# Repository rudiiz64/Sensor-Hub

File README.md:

# Sensor-Hub

__Purpose:__ The purpose of this design is to start with an idea and see it to completion. Realistically, this sensor hub serves no real purpose, as it is mainly a way for me to begin initial schematic design and layout. This design tackles a multitude of areas that needed to be practiced, such as component selection, power distribution, and further acquiring data from datasheets.

This system utilizes an STM32L100 chip with an active reset and boot mode toggle, USB-B receptacle, onboard sensors, which include light intensity, humiditiy, and ambient temperature, an SD card, SWD breakout pins, a +5V to +3.3V linear voltage regulator, a screw terminal to fit a +5V battery with a protective eFuse, and a battery recharge circuit.

__Lessons learned:__ One of the most valuable lessons learned while progressing through this project is to fully understand what the system needs and whether or not those needs can be met. This means providing proper current, minimizing voltage drop due to trace length/width, and also understanding return current. Another notable lesson is that sometimes designs can be a little weird due to component placement. From my experience, the initial component placement will not result in the greatest system, as my original design had a voltage drop of 0.4V in the 3.3V line due to excessive trace lengths. Lastly, I learned that more time needs to be spent on designing the power side in terms of component selection AND feasibility. For instance, the design was originally only USB powered, which made no real sense as these kinds of sensors need to be flexible in terms of placement. Because of this reasoning, a battery was implemented with a battery recharge and a protective eFuse.

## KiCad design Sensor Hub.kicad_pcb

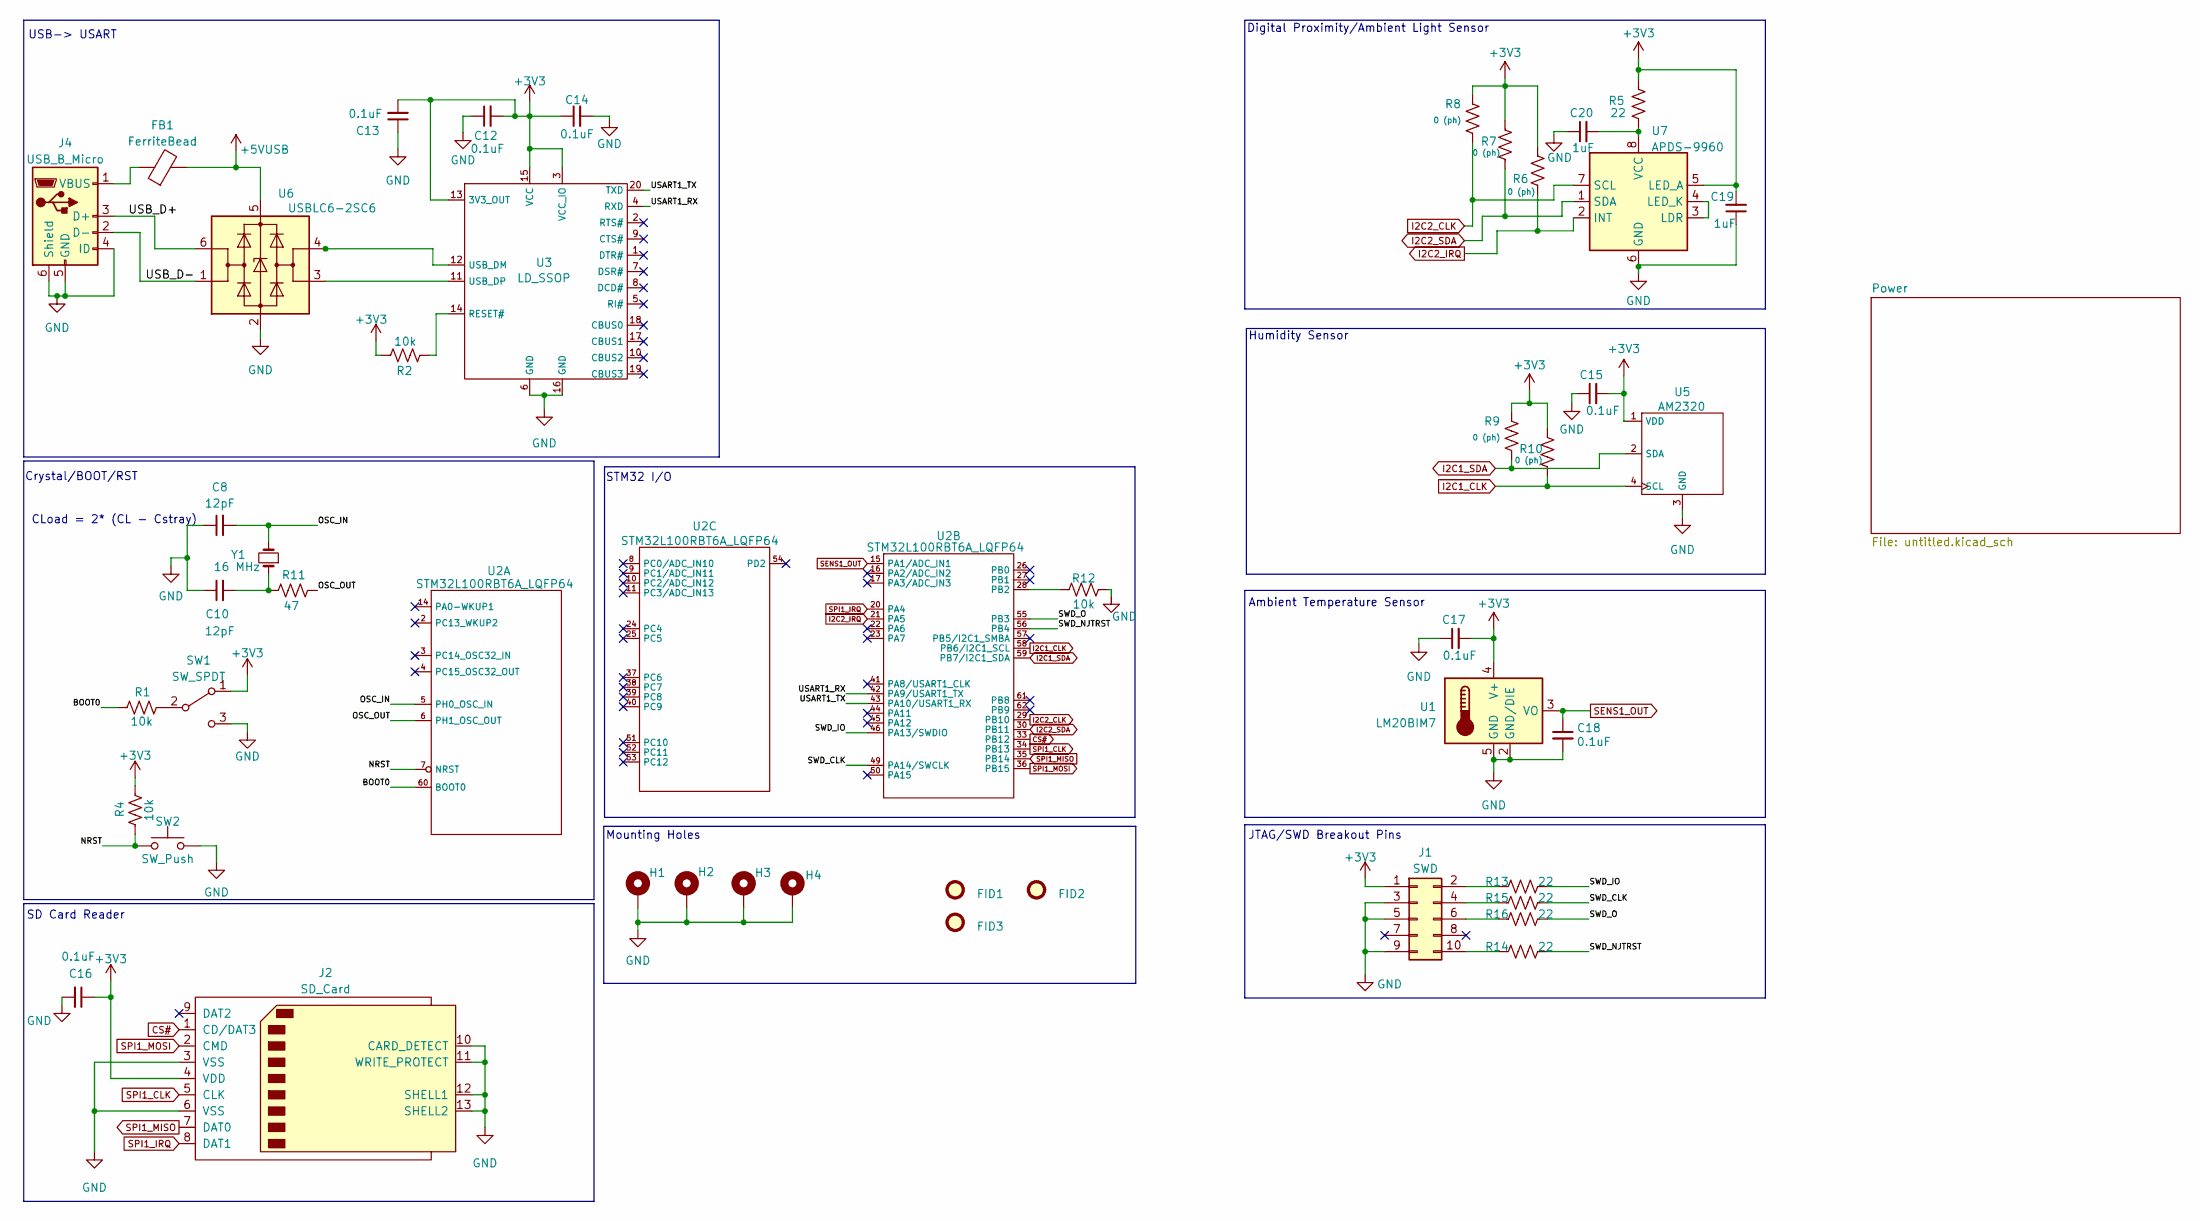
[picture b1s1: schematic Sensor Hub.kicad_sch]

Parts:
C8, C10: 12pF; C_0402_1005Metric
C12, C13, C14, C15, C16, C17, C18: 0.1uF; C_0603_1608Metric
C19, C20: 1uF; C_0603_1608Metric
FB1: FerriteBead; LairdTech_28C0236-0JW-10
FID1, FID2, FID3: Fiducial; Fiducial_1mm_Mask2mm
H1, H2, H3, H4: MountingHole_Pad; MountingHole_2.2mm_M2_Pad_Via
J1: SWD; PinHeader_2x05_P2.00mm_Vertical
J2: SD_Card; SD_Hirose_DM1AA_SF_PEJ82
J4: USB_B_Micro; USB_Micro-B_Amphenol_10118194_Horizontal
R1, R2, R4, R12: 10k; R_0402_1005Metric
R5, R13, R14, R15, R16: 22; R_0402_1005Metric
R6, R7, R8, R9, R10: 0 (ph); R_0402_1005Metric
R11: 47; R_0402_1005Metric
SW1: SW_SPDT; SW_E-Switch_EG1271_SPDT
SW2: SW_Push; SW_PUSH_6mm
U1: LM20BIM7; SOT-353_SC-70-5
U2: STM32L100RBT6A_LQFP64
U3: LD_SSOP; FT231_20_LD_SSOP
U5: AM2320; PinSocket_1x04_P2.00mm_Vertical
U6: USBLC6-2SC6; SOT-23-6
U7: APDS-9960; Avago_APDS-9960
Y1: 16 MHz; Crystal_SMD_0603-2Pin_6.0x3.5mm

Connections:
+3V3: C12.2, C13.2, C14.1, C15.2, C16.1, C17.2, C19.2, J1.1, J2.4 (VDD), R2.1, R4.1, R5.2, R6.2, R7.2, R8.2, R9.2, R10.2, SW1.1 (A), U1.4 (V+), U3.3 (VCC_IO), U3.13 (3V3_OUT), U3.15 (VCC), U5.1 (VDD), U7.5 (LED_A); also elsewhere on the board
+5V: FB1.2, U6.5 (VBUS); also elsewhere on the board
/BOOT0: R1.2, U2.60 (BOOT0)
/NRST: R4.2, SW2.1, U2.7 (NRST)
/OSC_IN: C8.2, U2.5 (PH0_OSC_IN), Y1.2
/OSC_OUT: R11.1, U2.6 (PH1_OSC_OUT)
/SWD_CLK: R15.2, U2.49 (PA14/SWCLK)
/SWD_IO: R13.1, U2.46 (PA13/SWDIO)
/SWD_NJTRST: R14.2, U2.56 (PB4)
/SWD_O: R16.2, U2.55 (PB3)
/USART1_RX: U2.42 (PA9/USART1_TX), U3.4 (RXD)
/USART1_TX: U2.43 (PA10/USART1_RX), U3.20 (TXD)
/USB_D+: J4.3 (D+), U6.6 (I/O1)
/USB_D-: J4.2 (D-), U6.1 (I/O1)
CS#: J2.1 (CD/DAT3), U2.33 (PB12)
GND: C8.1, C10.1, C12.1, C13.1, C14.2, C15.1, C16.2, C17.1, C18.2, C19.1, C20.1, H1.1, H2.1, H3.1, H4.1, J1.3, J1.5, J1.9, J2.3 (VSS), J2.6 (VSS), J2.10 (CARD_DETECT), J2.11 (WRITE_PROTECT), J2.12 (SHELL1), J2.13 (SHELL2), J2.CP, J2.SH, J2.SW, J2.WP, J4.4 (ID), J4.5 (GND), J4.6 (Shield), R12.2, SW1.3 (C), SW2.2, U1.2 (GND/DIE), U1.5 (GND), U3.6 (GND), U3.16 (GND), U5.3 (GND), U6.2 (GND), U7.6 (GND); also elsewhere on the board
I2C1_CLK: R10.1, U2.58 (PB6/I2C1_SCL), U5.4 (SCL)
I2C1_SDA: R9.1, U2.59 (PB7/I2C1_SDA), U5.2 (SDA)
I2C2_CLK: R8.1, U2.29 (PB10), U7.7 (SCL)
I2C2_IRQ: R6.1, U2.21 (PA5), U7.2 (INT)
I2C2_SDA: R7.1, U2.30 (PB11), U7.1 (SDA)
unnamed: C10.2, R11.2, Y1.1
unnamed: J1.2, R13.2
unnamed: J1.4, R15.1
unnamed: J1.6, R16.1
unnamed: J1.10, R14.1
unnamed: FB1.1, J4.1 (VBUS)
unnamed: R1.1, SW1.2 (B)
unnamed: R12.1, U2.28 (PB2)
unnamed: R2.2, U3.14 (RESET#)
unnamed: U3.12 (USB_DM), U6.4 (I/O2)
unnamed: U3.11 (USB_DP), U6.3 (I/O2)
unnamed: U7.3 (LDR), U7.4 (LED_K)
unnamed: C20.2, R5.1, U7.8 (VCC)
SENS1_OUT: C18.1, U1.3 (VO), U2.15 (PA1/ADC_IN1)
SPI1_CLK: J2.5 (CLK), U2.34 (PB13)
SPI1_IRQ: J2.8 (DAT1), U2.20 (PA4)
SPI1_MISO: J2.7 (DAT0), U2.35 (PB14)
SPI1_MOSI: J2.2 (CMD), U2.36 (PB15)

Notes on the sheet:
STM32 I/O
Crystal/BOOT/RST
CLoad = 2* (CL - Cstray)
Mounting Holes
Ambient Temperature Sensor
Digital Proximity/Ambient Light Sensor
JTAG/SWD Breakout Pins
SD Card Reader
Humidity Sensor
USB-> USART

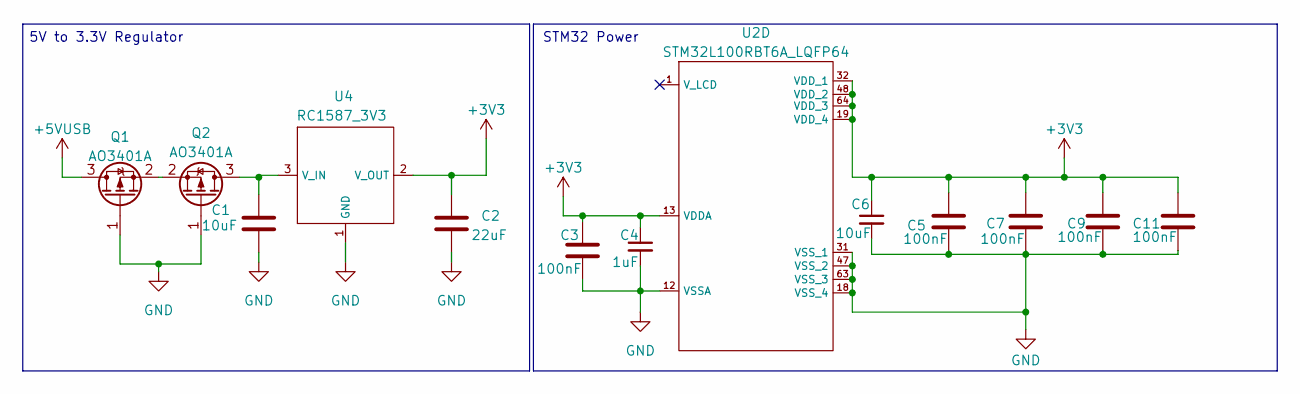
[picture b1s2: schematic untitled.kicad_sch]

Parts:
C1, C6: 10uF; C_0603_1608Metric
C2: 22uF; C_0603_1608Metric
C3, C5, C7, C9, C11: 100nF; C_0402_1005Metric
C4: 1uF; C_0603_1608Metric
Q1, Q2: AO3401A; SOT-23
U2: STM32L100RBT6A_LQFP64
U4: RC1587_3V3; RC1587M3V3T

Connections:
+3V3: C2.1, C3.1, C4.1, C5.1, C6.1, C7.1, C9.1, C11.1, U2.13 (VDDA), U2.19 (VDD_4), U2.32 (VDD_1), U2.48 (VDD_2), U2.64 (VDD_3), U4.2 (V_OUT); also elsewhere on the board
+5V: Q1.3 (D); also elsewhere on the board
GND: C1.2, C2.2, C3.2, C4.2, C5.2, C6.2, C7.2, C9.2, C11.2, Q1.1 (G), Q2.1 (G), U2.12 (VSSA), U2.18 (VSS_4), U2.31 (VSS_1), U2.47 (VSS_2), U2.63 (VSS_3), U4.1 (GND); also elsewhere on the board
unnamed: Q1.2 (S), Q2.2 (S)
unnamed: C1.1, Q2.3 (D), U4.3 (V_IN)

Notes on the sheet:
STM32 Power
5V to 3.3V Regulator

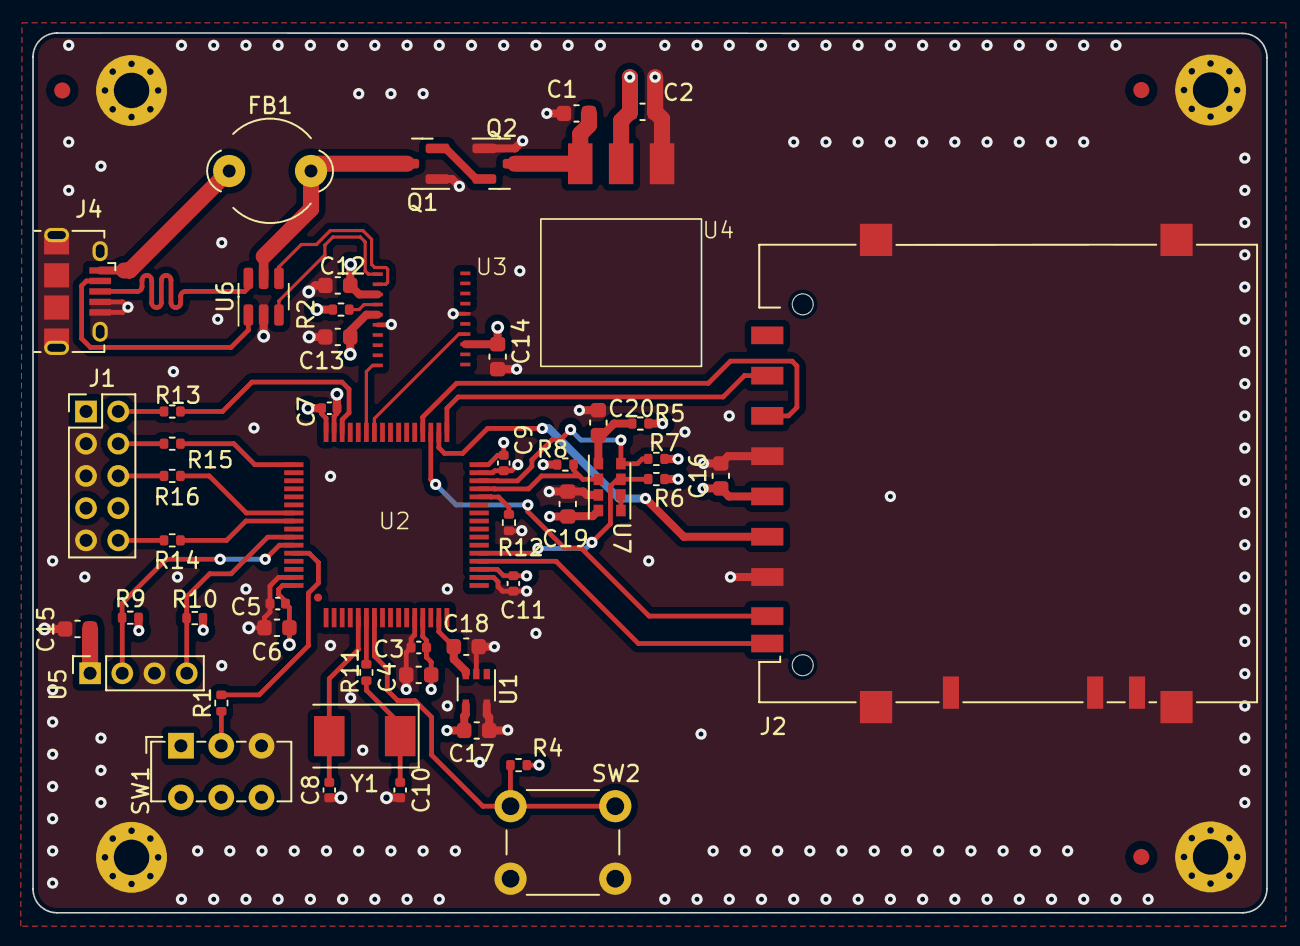
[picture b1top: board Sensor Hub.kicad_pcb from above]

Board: 4 copper layers, 76.6 x 54.6 mm, 58 parts (0 on the bottom side), 41 nets.

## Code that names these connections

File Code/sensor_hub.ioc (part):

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Mcu.Name=STM32H745ZITx
Mcu.Package=LQFP144
Mcu.UserName=STM32H745ZITx
PA1.GPIOParameters=PinAttribute
PA1.Mode=RMII
PA1.PinAttribute=CortexM7
PA1.Signal=ETH_REF_CLK
PA11.GPIOParameters=PinAttribute
PA11.Mode=Device_Only
PA11.PinAttribute=CortexM7
PA11.Signal=USB_OTG_FS_DM
PA12.GPIOParameters=PinAttribute
PA12.Mode=Device_Only
PA12.PinAttribute=CortexM7
PA12.Signal=USB_OTG_FS_DP
PA2.GPIOParameters=PinAttribute
PA2.Mode=RMII
PA2.PinAttribute=CortexM7
PA2.Signal=ETH_MDIO
PA7.GPIOParameters=PinAttribute
PA7.Mode=RMII
PA7.PinAttribute=CortexM7
PA7.Signal=ETH_CRS_DV
PA8.GPIOParameters=PinAttribute
PA8.Mode=Activate_SOF_FS
PA8.PinAttribute=CortexM7
PA8.Signal=USB_OTG_FS_SOF
PA9.GPIOParameters=PinAttribute
PA9.Mode=Activate_VBUS
PA9.PinAttribute=CortexM7
PA9.Signal=USB_OTG_FS_VBUS
PB0.ContextOwner=CortexM7
PB0.GPIOParameters=GPIO_Speed,GPIO_Label,PinAttribute
PB0.GPIO_Label=LD1 [Green Led]
PB0.GPIO_Speed=GPIO_SPEED_FREQ_VERY_HIGH
PB0.PinAttribute=CortexM7
PB0.Signal=GPIO_Output
PB13.GPIOParameters=PinAttribute
PB13.Mode=RMII
PB13.PinAttribute=CortexM7
PB13.Signal=ETH_TXD1
PB14.ContextOwner=CortexM7
PB14.GPIOParameters=GPIO_Speed,GPIO_Label,PinAttribute
PB14.GPIO_Label=LD3 [Red Led]
PB14.GPIO_Speed=GPIO_SPEED_FREQ_VERY_HIGH
PB14.PinAttribute=CortexM7
PB14.Signal=GPIO_Output
PB6.GPIOParameters=PinAttribute
PB6.Mode=I2C
PB6.PinAttribute=CortexM7
PB6.Signal=I2C1_SCL
PB7.GPIOParameters=PinAttribute
PB7.Mode=I2C
PB7.PinAttribute=CortexM7
PB7.Signal=I2C1_SDA
PC1.GPIOParameters=PinAttribute
PC1.Mode=RMII
PC1.PinAttribute=CortexM7
PC1.Signal=ETH_MDC
PC13.GPIOParameters=GPIO_Label,PinAttribute
PC13.GPIO_Label=B1 [Blue PushButton]
PC13.PinAttribute=Free
PC13.Signal=GPIO_Input
PC14-OSC32_IN\ (OSC32_IN).GPIOParameters=PinAttribute
PC14-OSC32_IN\ (OSC32_IN).Mode=LSE-External-Oscillator
PC14-OSC32_IN\ (OSC32_IN).PinAttribute=CortexM7
PC14-OSC32_IN\ (OSC32_IN).Signal=RCC_OSC32_IN
PC15-OSC32_OUT\ (OSC32_OUT).GPIOParameters=PinAttribute
PC15-OSC32_OUT\ (OSC32_OUT).Mode=LSE-External-Oscillator
PC15-OSC32_OUT\ (OSC32_OUT).PinAttribute=CortexM7
PC15-OSC32_OUT\ (OSC32_OUT).Signal=RCC_OSC32_OUT
PC4.GPIOParameters=PinAttribute
PC4.Mode=RMII
PC4.PinAttribute=CortexM7
PC4.Signal=ETH_RXD0
PC5.GPIOParameters=PinAttribute
PC5.Mode=RMII
PC5.PinAttribute=CortexM7
PC5.Signal=ETH_RXD1
PD10.GPIOParameters=GPIO_Label,PinAttribute
PD10.GPIO_Label=USB_OTG_FS_PWR_EN
PD10.PinAttribute=Free
PD10.Signal=GPIO_Output
PD8.GPIOParameters=GPIO_Label,PinAttribute
PD8.GPIO_Label=STLINK_RX
PD8.Mode=Asynchronous
PD8.PinAttribute=CortexM7
PD8.Signal=USART3_TX
PD9.GPIOParameters=GPIO_Label,PinAttribute
PD9.GPIO_Label=STLINK_TX
PD9.Mode=Asynchronous
PD9.PinAttribute=CortexM7
PD9.Signal=USART3_RX
PE1.GPIOParameters=GPIO_Label,PinAttribute
PE1.GPIO_Label=LD2 [Yellow Led]
PE1.PinAttribute=Free
PE1.Signal=GPIO_Output
PG11.GPIOParameters=PinAttribute
PG11.Mode=RMII
PG11.PinAttribute=CortexM7
PG11.Signal=ETH_TX_EN
PG13.GPIOParameters=PinAttribute
PG13.Mode=RMII
PG13.PinAttribute=CortexM7
PG13.Signal=ETH_TXD0
PG7.GPIOParameters=GPIO_Label,PinAttribute
PG7.GPIO_Label=USB_OTG_FS_OVCR
PG7.PinAttribute=Free
PG7.Signal=GPXTI7
PH0-OSC_IN\ (PH0).GPIOParameters=PinAttribute
PH0-OSC_IN\ (PH0).Mode=HSE-External-Clock-Source
PH0-OSC_IN\ (PH0).PinAttribute=CortexM7
PH0-OSC_IN\ (PH0).Signal=RCC_OSC_IN
PH1-OSC_OUT\ (PH1).GPIOParameters=PinAttribute
PH1-OSC_OUT\ (PH1).PinAttribute=CortexM7
PH1-OSC_OUT\ (PH1).Signal=RCC_OSC_OUT
RCC.HSE_VALUE=8000000
RCC.SYSCLKFreq_VALUE=80000000
RCC.SYSCLKSource=RCC_SYSCLKSOURCE_PLLCLK
board=NUCLEO-H745ZI-Q
boardIOC=true

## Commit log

2023-03-12 Initial push
    Rev 0.1
    - Initial schematic
2023-03-12 Update to schem
    - Updated per Adi's feedback
2023-03-13 Updated Schematic
    - Added LTC4002 battery management IC
    - Updated previous ICs to reflect given feedback
2023-03-20 Rev 0.3
    + Updated schematic to reflect utilization of USB-B micro instead of USB-C
    + Began initial layout of PCB
    - Need to look into eFuse layout, as specified layout recommendation utilizes ground pours
    - Need to update SD Card footprint as pads are not linked
2023-03-29 Rev 1.0
    + Initial PCB board completed
2023-04-03 Updated to Rev 1.1
    + Adjusted trace widths to appropriately fit IC pads while supporting wanted current and minimizing vdrop
    + Adjusted edge cuts of PCB to remove unnecessary areas
2023-09-21 Updated Rev 2.0
    + Revamped board to 4 layer with components on both signal layers (top/bottom)
    + Adjusted compactness of components, reducing size by approx 30%
    + Added mounting holes for mounting purposes
    - Removed battery, batt charger, eFuse (USB driven only)
2023-12-04 Rev 0.1 Code
    + Added initial code for BMP180 (I2C) on STM32Cube
2024-01-08 Updated to Rev B
    + Added ESD protection on USB side
    + Redesigned board layout to a SIG/GND/GND/SIG stack up and using L4 as 3V3 plane
    + Resized capacitors and resistors to 0402
    + Added 3D models of certain components
    + Added ferrite bead to 5V line
